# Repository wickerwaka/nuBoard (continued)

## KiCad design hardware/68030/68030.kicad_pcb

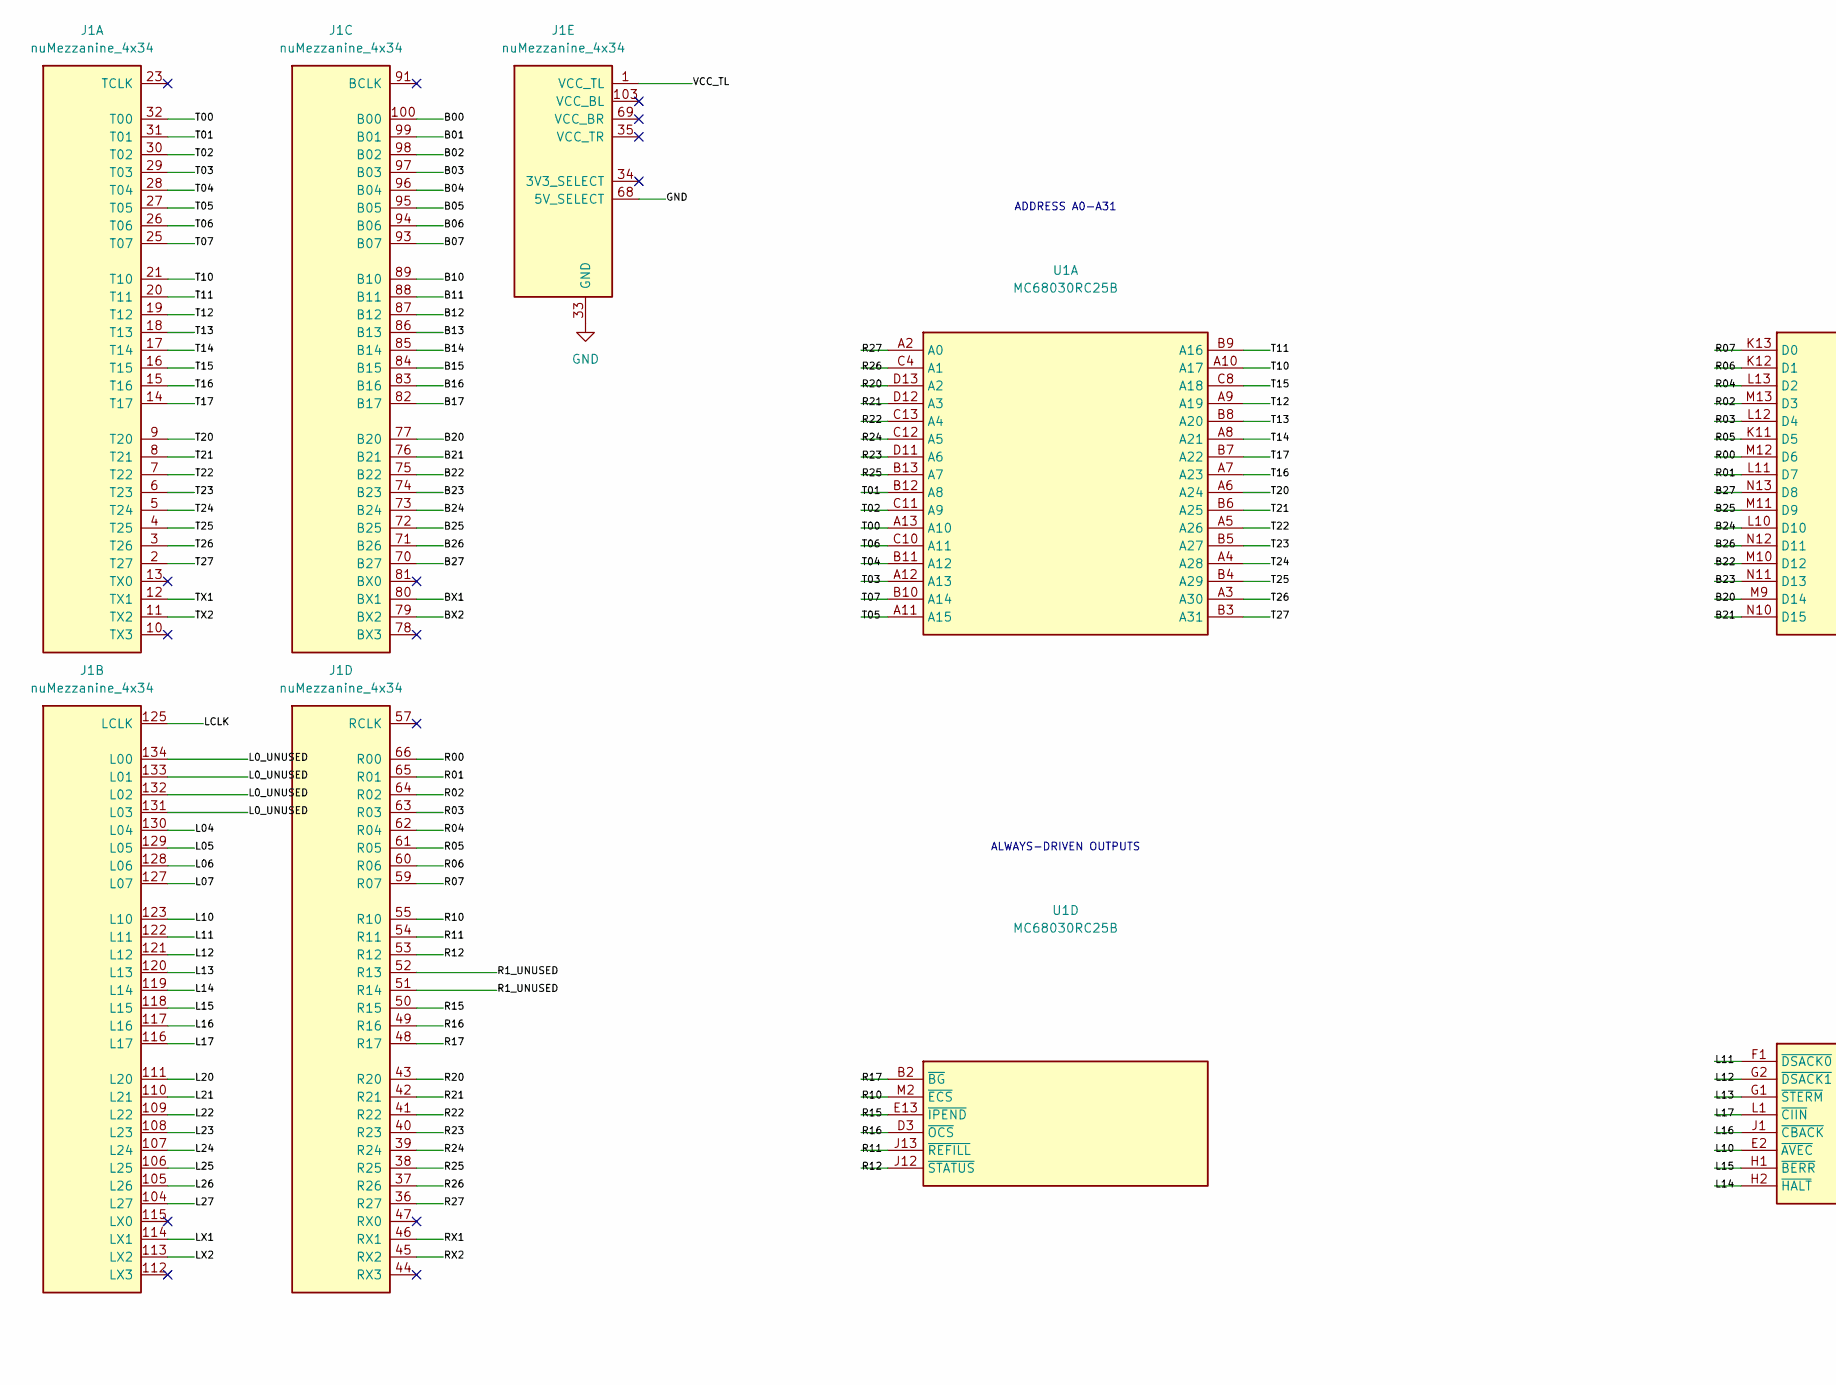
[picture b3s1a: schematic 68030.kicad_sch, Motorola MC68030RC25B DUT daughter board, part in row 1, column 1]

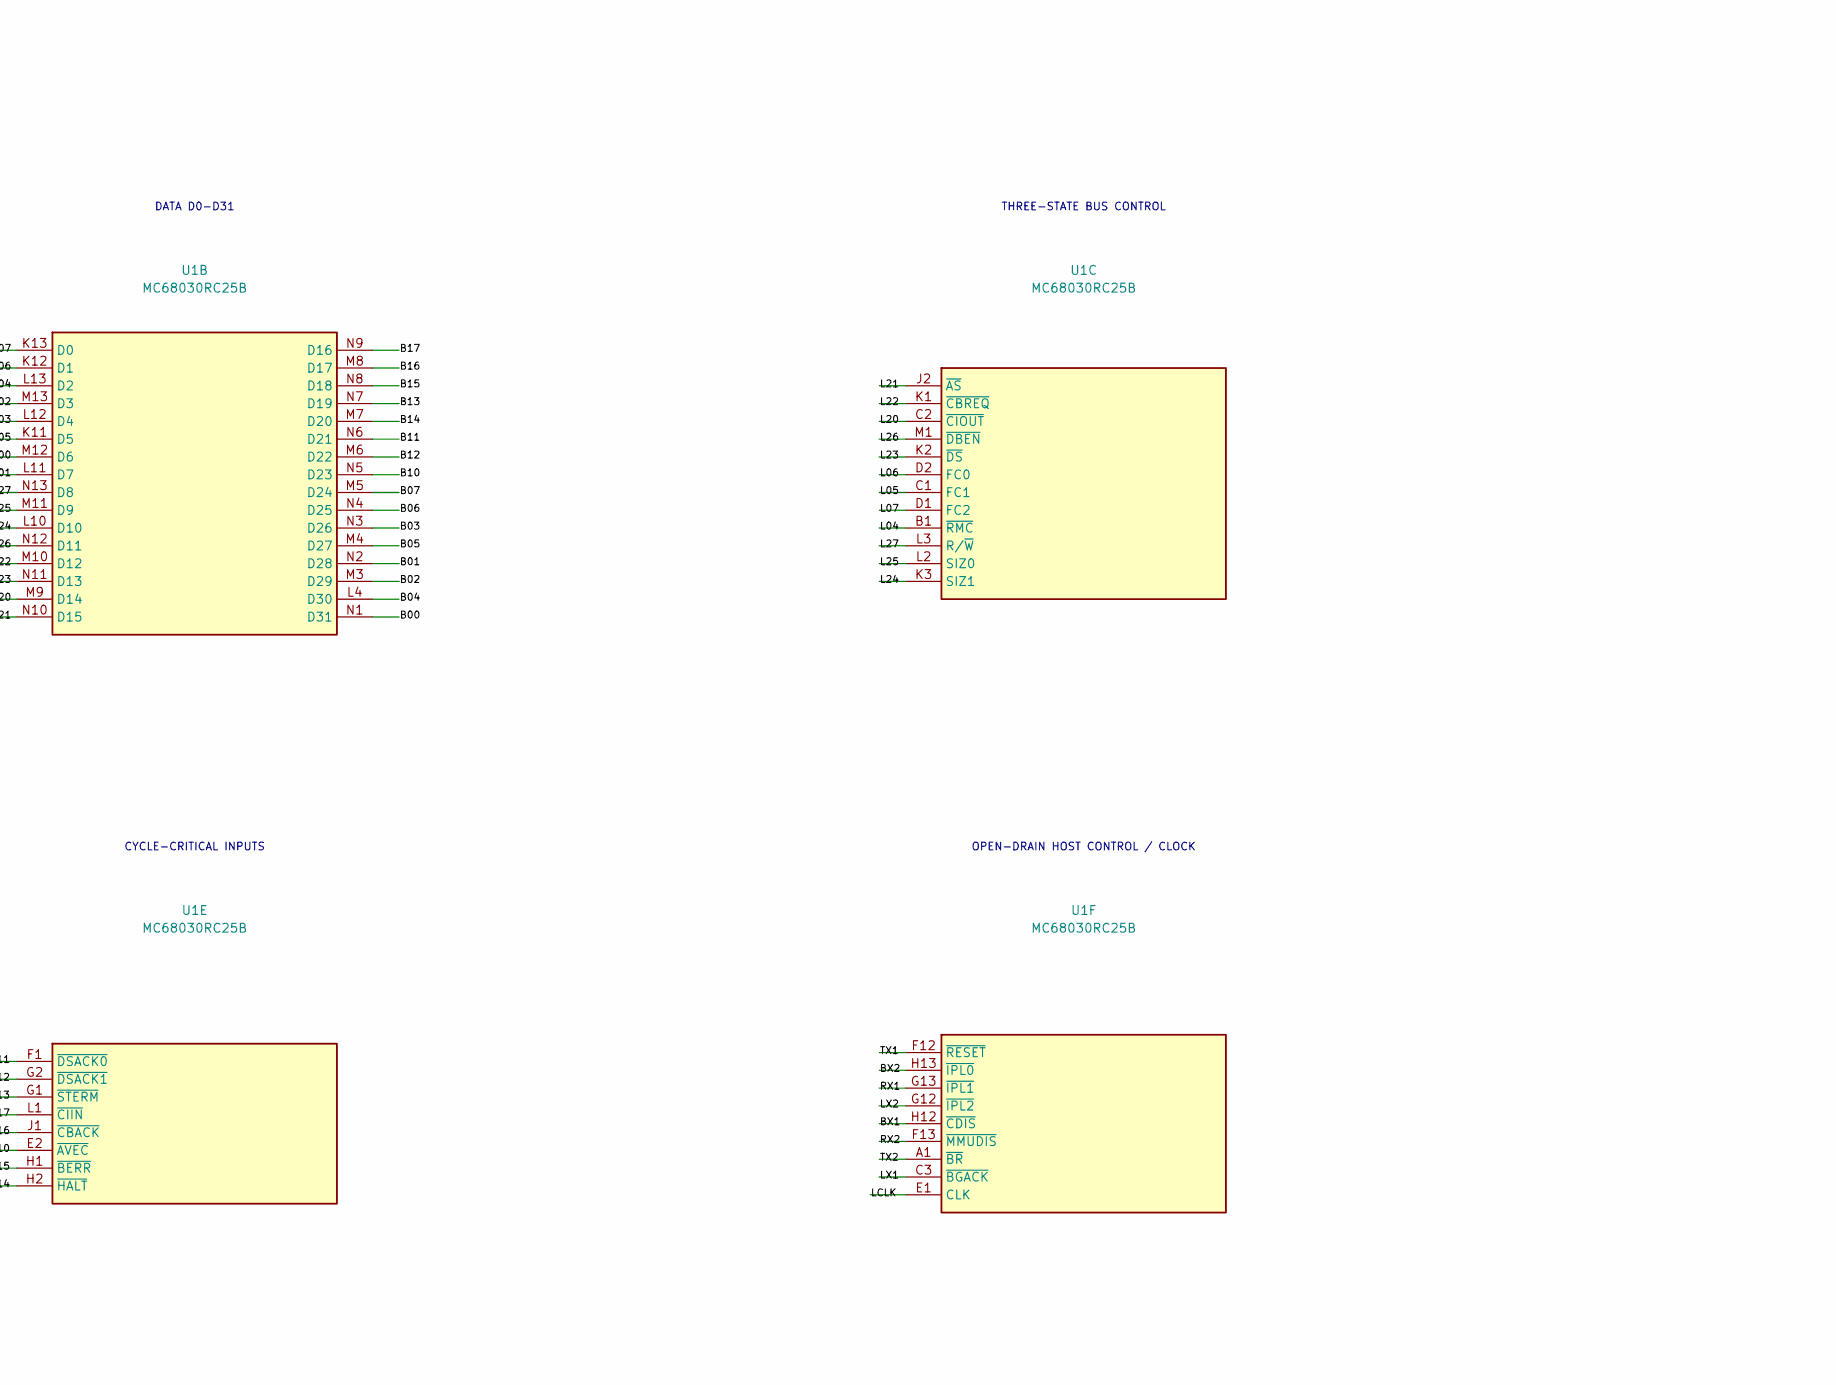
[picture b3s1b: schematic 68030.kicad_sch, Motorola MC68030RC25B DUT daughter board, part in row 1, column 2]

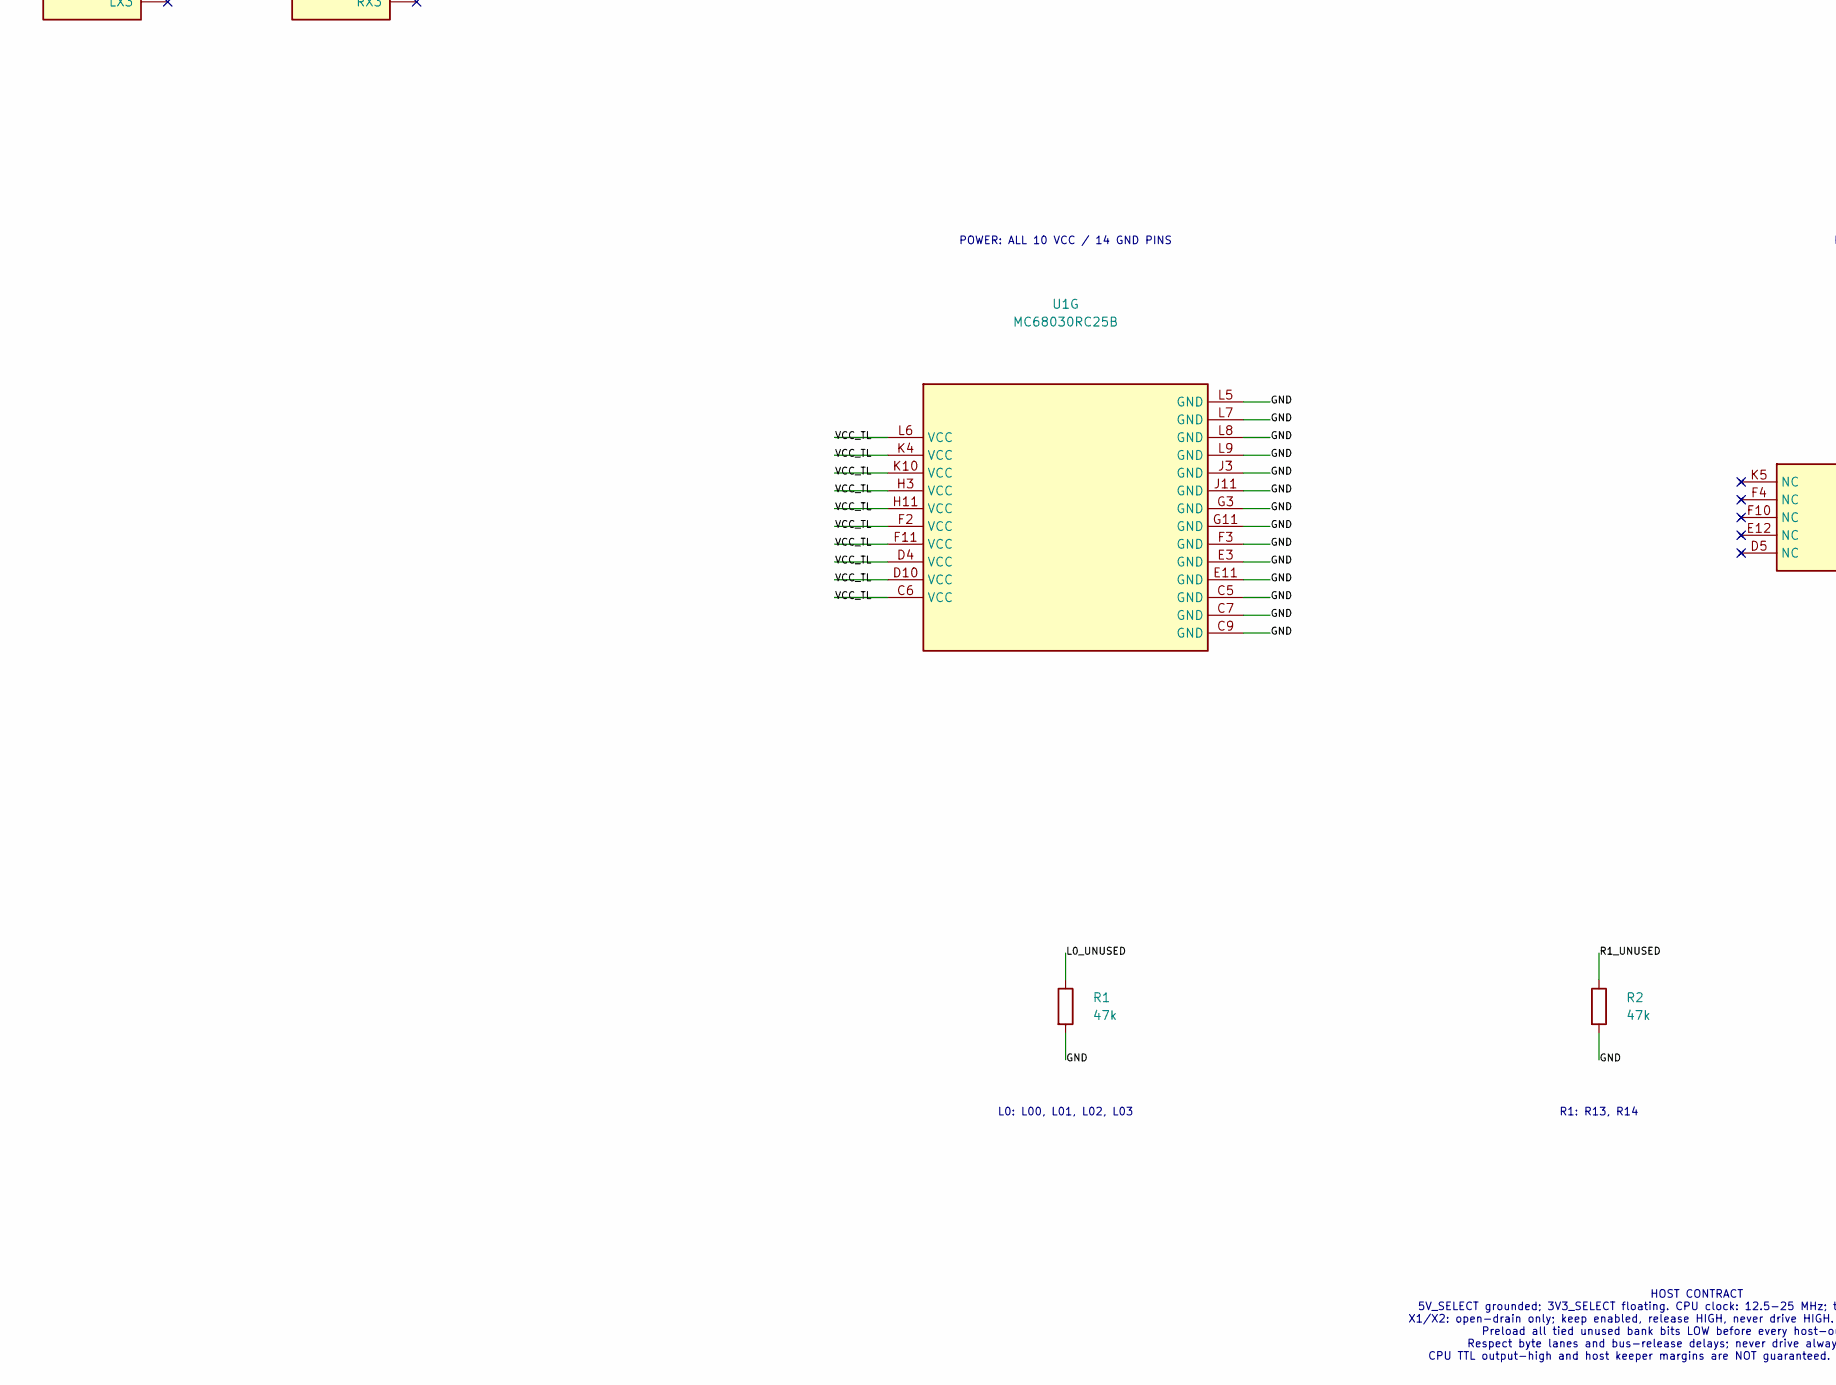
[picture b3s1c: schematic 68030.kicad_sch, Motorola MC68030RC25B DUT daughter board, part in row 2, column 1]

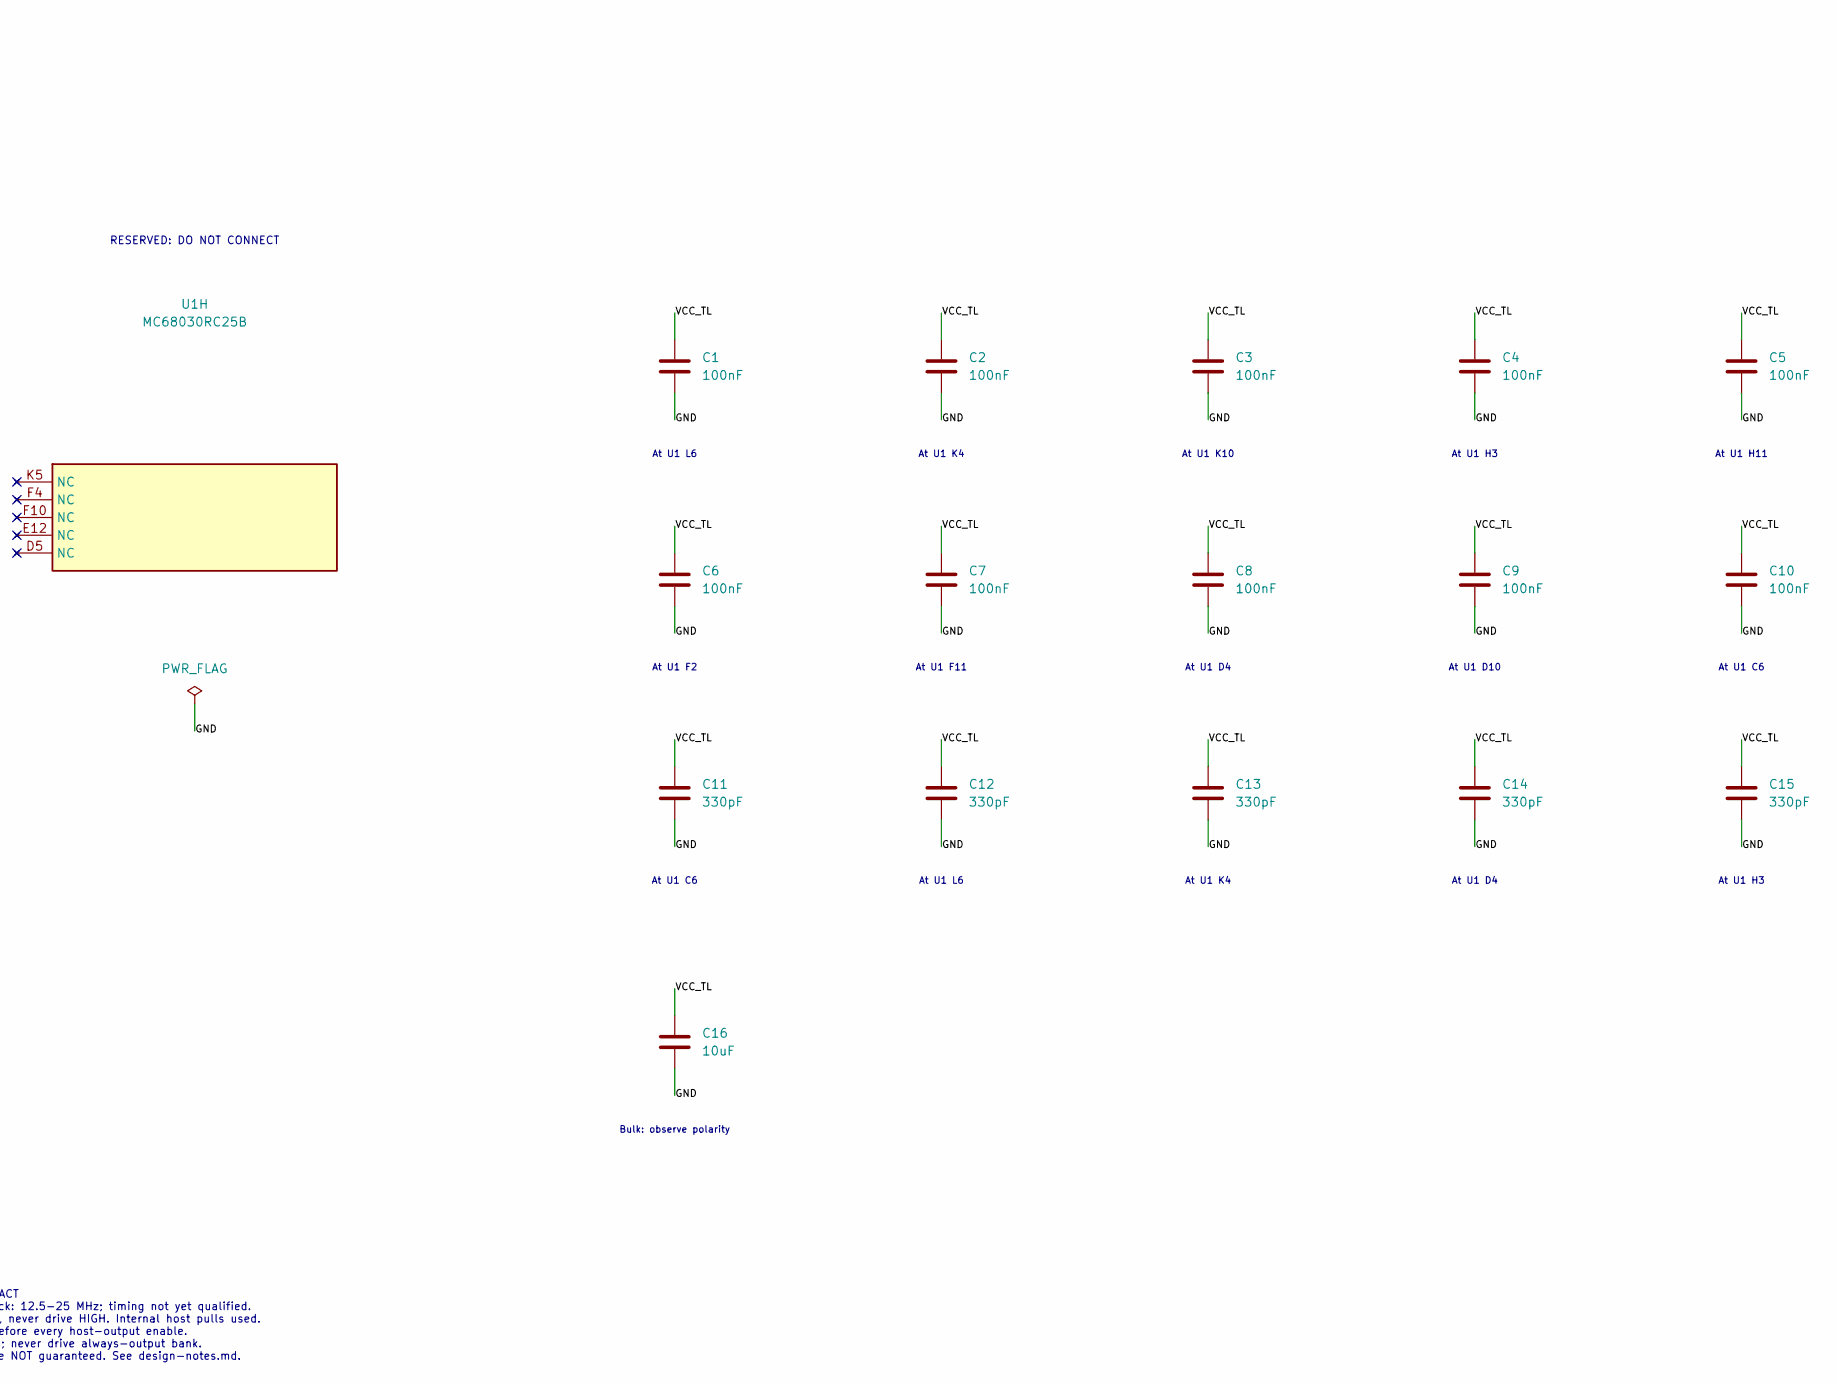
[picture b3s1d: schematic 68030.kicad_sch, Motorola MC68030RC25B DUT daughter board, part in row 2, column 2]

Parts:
C1, C2, C3, C4, C5, C6, C7, C8, C9, C10: 100nF; C_0805_2012Metric_Pad1.18x1.45mm_HandSolder; Voltage 50V
C11, C12, C13, C14, C15: 330pF; C_0805_2012Metric_Pad1.18x1.45mm_HandSolder; Voltage 50V
C16: 10uF; C_0805_2012Metric_Pad1.18x1.45mm_HandSolder; Voltage 25V
J1: nuMezzanine_4x34; nuMezzanine_4x34_P2.54mm
R1, R2: 47k; R_0805_2012Metric_Pad1.20x1.40mm_HandSolder
U1: MC68030RC25B; CPGA-128_MC68030_RC

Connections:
/B00: J1.100 (B00_100), U1.N1 (D31)
/B01: J1.99 (B01_99), U1.N2 (D28)
/B02: J1.98 (B02_98), U1.M3 (D29)
/B03: J1.97 (B03_97), U1.N3 (D26)
/B04: J1.96 (B04_96), U1.L4 (D30)
/B05: J1.95 (B05_95), U1.M4 (D27)
/B06: J1.94 (B06_94), U1.N4 (D25)
/B07: J1.93 (B07_93), U1.M5 (D24)
/B10: J1.89 (B10_89), U1.N5 (D23)
/B11: J1.88 (B11_88), U1.N6 (D21)
/B12: J1.87 (B12_87), U1.M6 (D22)
/B13: J1.86 (B13_86), U1.N7 (D19)
/B14: J1.85 (B14_85), U1.M7 (D20)
/B15: J1.84 (B15_84), U1.N8 (D18)
/B16: J1.83 (B16_83), U1.M8 (D17)
/B17: J1.82 (B17_82), U1.N9 (D16)
/B20: J1.77 (B20_77), U1.M9 (D14)
/B21: J1.76 (B21_76), U1.N10 (D15)
/B22: J1.75 (B22_75), U1.M10 (D12)
/B23: J1.74 (B23_74), U1.N11 (D13)
/B24: J1.73 (B24_73), U1.L10 (D10)
/B25: J1.72 (B25_72), U1.M11 (D9)
/B26: J1.71 (B26_71), U1.N12 (D11)
/B27: J1.70 (B27_70), U1.N13 (D8)
/BX1: J1.80 (BX1_80), U1.H12 (~CDIS)
/BX2: J1.79 (BX2_79), U1.H13 (~IPL0)
/L0_UNUSED: J1.131 (L03_131), J1.132 (L02_132), J1.133 (L01_133), J1.134 (L00_134), R1.1
/L04: J1.130 (L04_130), U1.B1 (~RMC)
/L05: J1.129 (L05_129), U1.C1 (FC1)
/L06: J1.128 (L06_128), U1.D2 (FC0)
/L07: J1.127 (L07_127), U1.D1 (FC2)
/L10: J1.123 (L10_123), U1.E2 (~AVEC)
/L11: J1.122 (L11_122), U1.F1 (~DSACK0)
/L12: J1.121 (L12_121), U1.G2 (~DSACK1)
/L13: J1.120 (L13_120), U1.G1 (~STERM)
/L14: J1.119 (L14_119), U1.H2 (~HALT)
/L15: J1.118 (L15_118), U1.H1 (~BERR)
/L16: J1.117 (L16_117), U1.J1 (~CBACK)
/L17: J1.116 (L17_116), U1.L1 (~CIIN)
/L20: J1.111 (L20_111), U1.C2 (~CIOUT)
/L21: J1.110 (L21_110), U1.J2 (~AS)
/L22: J1.109 (L22_109), U1.K1 (~CBREQ)
/L23: J1.108 (L23_108), U1.K2 (~DS)
/L24: J1.107 (L24_107), U1.K3 (SIZ1)
/L25: J1.106 (L25_106), U1.L2 (SIZ0)
/L26: J1.105 (L26_105), U1.M1 (~DBEN)
/L27: J1.104 (L27_104), U1.L3 (R/~W)
/LCLK: J1.125 (LCLK_125), U1.E1 (CLK)
/LX1: J1.114 (LX1_114), U1.C3 (~BGACK)
/LX2: J1.113 (LX2_113), U1.G12 (~IPL2)
/R00: J1.66 (R00_66), U1.M12 (D6)
/R01: J1.65 (R01_65), U1.L11 (D7)
/R1_UNUSED: J1.51 (R14_51), J1.52 (R13_52), R2.1
/R02: J1.64 (R02_64), U1.M13 (D3)
/R03: J1.63 (R03_63), U1.L12 (D4)
/R04: J1.62 (R04_62), U1.L13 (D2)
/R05: J1.61 (R05_61), U1.K11 (D5)
/R06: J1.60 (R06_60), U1.K12 (D1)
/R07: J1.59 (R07_59), U1.K13 (D0)
/R10: J1.55 (R10_55), U1.M2 (~ECS)
/R11: J1.54 (R11_54), U1.J13 (~REFILL)
/R12: J1.53 (R12_53), U1.J12 (~STATUS)
/R15: J1.50 (R15_50), U1.E13 (~IPEND)
/R16: J1.49 (R16_49), U1.D3 (~OCS)
/R17: J1.48 (R17_48), U1.B2 (~BG)
/R20: J1.43 (R20_43), U1.D13 (A2)
/R21: J1.42 (R21_42), U1.D12 (A3)
/R22: J1.41 (R22_41), U1.C13 (A4)
/R23: J1.40 (R23_40), U1.D11 (A6)
/R24: J1.39 (R24_39), U1.C12 (A5)
/R25: J1.38 (R25_38), U1.B13 (A7)
/R26: J1.37 (R26_37), U1.C4 (A1)
/R27: J1.36 (R27_36), U1.A2 (A0)
/RX1: J1.46 (RX1_46), U1.G13 (~IPL1)
/RX2: J1.45 (RX2_45), U1.F13 (~MMUDIS)
/T00: J1.32 (T00_32), U1.A13 (A10)
/T01: J1.31 (T01_31), U1.B12 (A8)
/T02: J1.30 (T02_30), U1.C11 (A9)
/T03: J1.29 (T03_29), U1.A12 (A13)
/T04: J1.28 (T04_28), U1.B11 (A12)
/T05: J1.27 (T05_27), U1.A11 (A15)
/T06: J1.26 (T06_26), U1.C10 (A11)
/T07: J1.25 (T07_25), U1.B10 (A14)
/T10: J1.21 (T10_21), U1.A10 (A17)
/T11: J1.20 (T11_20), U1.B9 (A16)
/T12: J1.19 (T12_19), U1.A9 (A19)
/T13: J1.18 (T13_18), U1.B8 (A20)
/T14: J1.17 (T14_17), U1.A8 (A21)
/T15: J1.16 (T15_16), U1.C8 (A18)
/T16: J1.15 (T16_15), U1.A7 (A23)
/T17: J1.14 (T17_14), U1.B7 (A22)
/T20: J1.9 (T20_9), U1.A6 (A24)
/T21: J1.8 (T21_8), U1.B6 (A25)
/T22: J1.7 (T22_7), U1.A5 (A26)
/T23: J1.6 (T23_6), U1.B5 (A27)
/T24: J1.5 (T24_5), U1.A4 (A28)
/T25: J1.4 (T25_4), U1.B4 (A29)
/T26: J1.3 (T26_3), U1.A3 (A30)
/T27: J1.2 (T27_2), U1.B3 (A31)
/TX1: J1.12 (TX1_12), U1.F12 (~RESET)
/TX2: J1.11 (TX2_11), U1.A1 (~BR)
/VCC_TL: C1.1, C2.1, C3.1, C4.1, C5.1, C6.1, C7.1, C8.1, C9.1, C10.1, C11.1, C12.1, C13.1, C14.1, C15.1, C16.1, J1.1 (VCC_TL_1), U1.C6 (VCC), U1.D4 (VCC), U1.D10 (VCC), U1.F2 (VCC), U1.F11 (VCC), U1.H3 (VCC), U1.H11 (VCC), U1.K4 (VCC), U1.K10 (VCC), U1.L6 (VCC)
GND: C1.2, C2.2, C3.2, C4.2, C5.2, C6.2, C7.2, C8.2, C9.2, C10.2, C11.2, C12.2, C13.2, C14.2, C15.2, C16.2, J1.22 (GND_22), J1.24 (GND_24), J1.33 (GND_33), J1.56 (GND_56), J1.58 (GND_58), J1.67 (GND_67), J1.68 (5V_SELECT_68), J1.90 (GND_90), J1.92 (GND_92), J1.101 (GND_101), J1.102 (GND), J1.124 (GND_124), J1.126 (GND_126), J1.135 (GND_135), J1.136 (GND), R1.2, R2.2, U1.C5 (GND), U1.C7 (GND), U1.C9 (GND), U1.E3 (GND), U1.E11 (GND), U1.F3 (GND), U1.G3 (GND), U1.G11 (GND), U1.J3 (GND), U1.J11 (GND), U1.L5 (GND), U1.L7 (GND), U1.L8 (GND), U1.L9 (GND)

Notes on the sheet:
ADDRESS A0-A31
DATA D0-D31
THREE-STATE BUS CONTROL
ALWAYS-DRIVEN OUTPUTS
CYCLE-CRITICAL INPUTS
OPEN-DRAIN HOST CONTROL / CLOCK
POWER: ALL 10 VCC / 14 GND PINS
RESERVED: DO NOT CONNECT
At U1 L6
At U1 K4
At U1 K10
At U1 H3
At U1 H11
At U1 F2
At U1 F11
At U1 D4
At U1 D10
At U1 C6
Bulk: observe polarity
L0: L00, L01, L02, L03
R1: R13, R14
HOST CONTRACT 5V_SELECT grounded; 3V3_SELECT floating. CPU clock: 12.5-25 MHz; timing not yet qualified. X1/X2: open-drain only; keep enabled, release HIGH, never drive HIGH. Internal host pulls used. Preload all tied unused bank bits LOW before every host-output enable. Respect byte lanes and bus-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

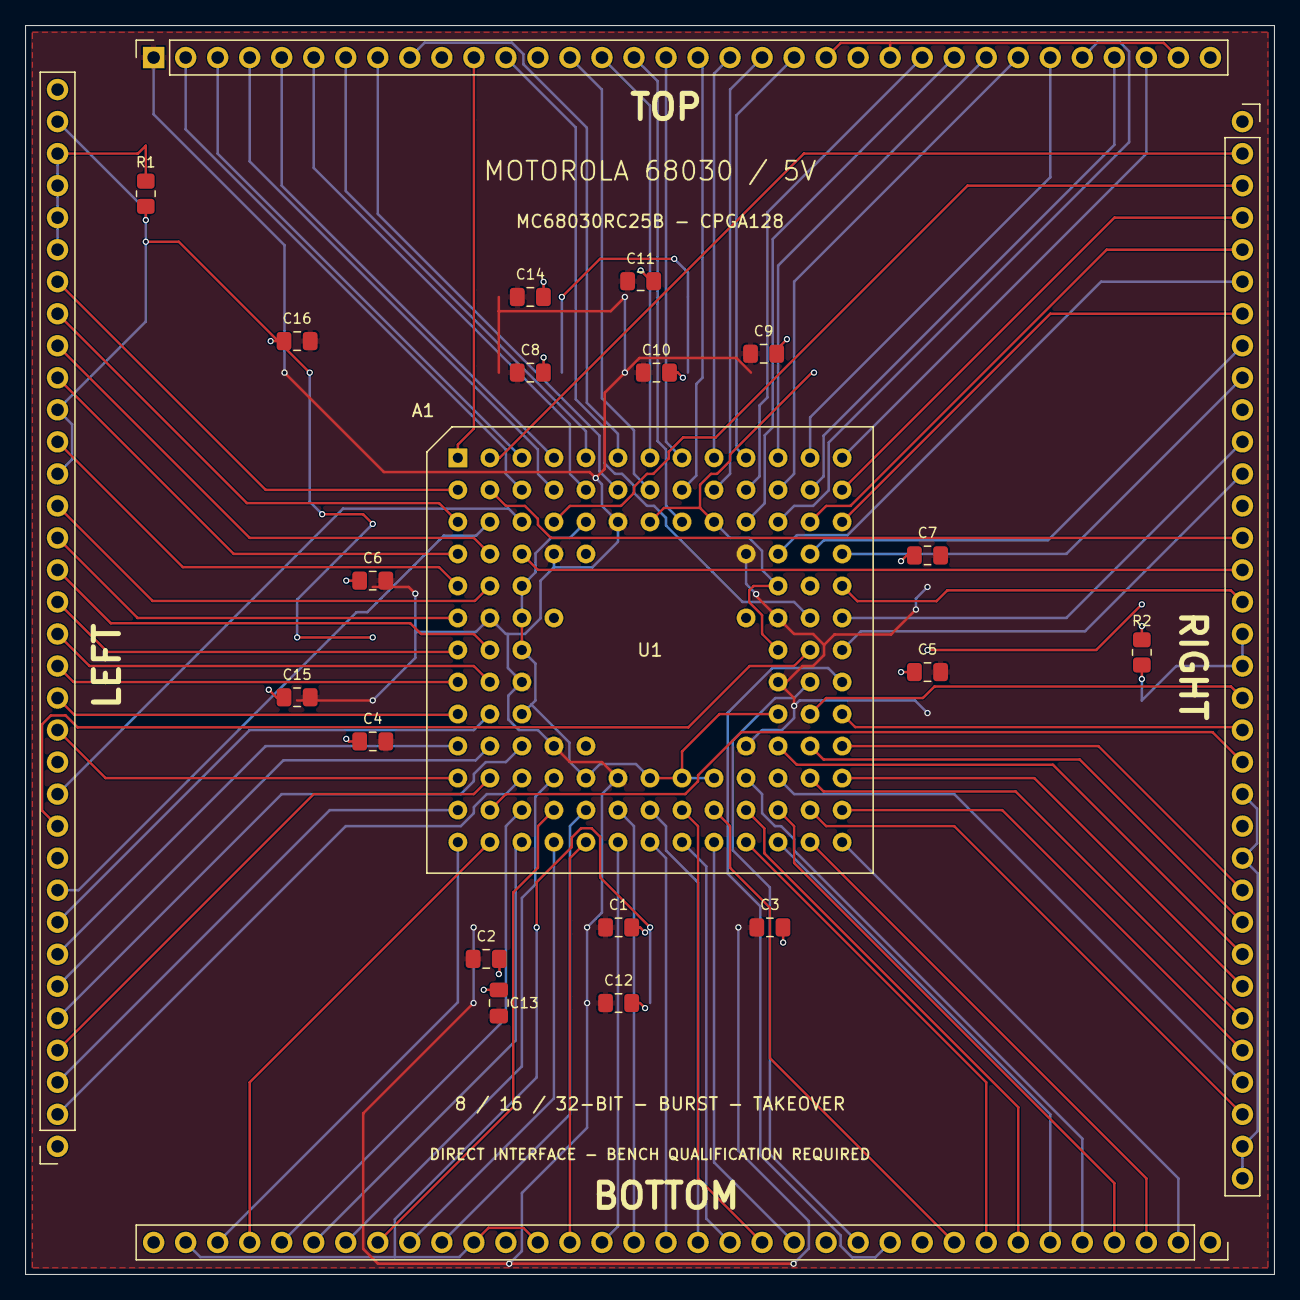
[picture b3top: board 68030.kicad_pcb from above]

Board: 2 copper layers, 99.1 x 99.1 mm, 20 parts (0 on the bottom side), 103 nets.

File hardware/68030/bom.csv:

References,Quantity,Value / part,Package,Notes
U1,1,Motorola MC68030RC25B,CPGA128 CASE789C-01,Direct CPU pin mounting; no socket qualified
C1 C2 C3 C4 C5 C6 C7 C8 C9 C10,10,100nF X7R ceramic >=50V,0805 SMD HandSolder,one per VCC pin
C11 C12 C13 C14 C15,5,330pF C0G ceramic >=50V,0805 SMD HandSolder,Supplementary high-frequency bypass; 0805 C0G
C16,1,10uF X7R/X5R MLCC >=25V,0805 SMD HandSolder,Nonpolar; check effective capacitance at 5V DC bias
R1 R2,2,47k 1% >=0.25W,0805 SMD HandSolder,One shared unused-bit pull-down per partially used bank
J1,1,nuBoard mating contact set,"Four 34-position rows, 2.54mm pitch",Match host mating geometry and height

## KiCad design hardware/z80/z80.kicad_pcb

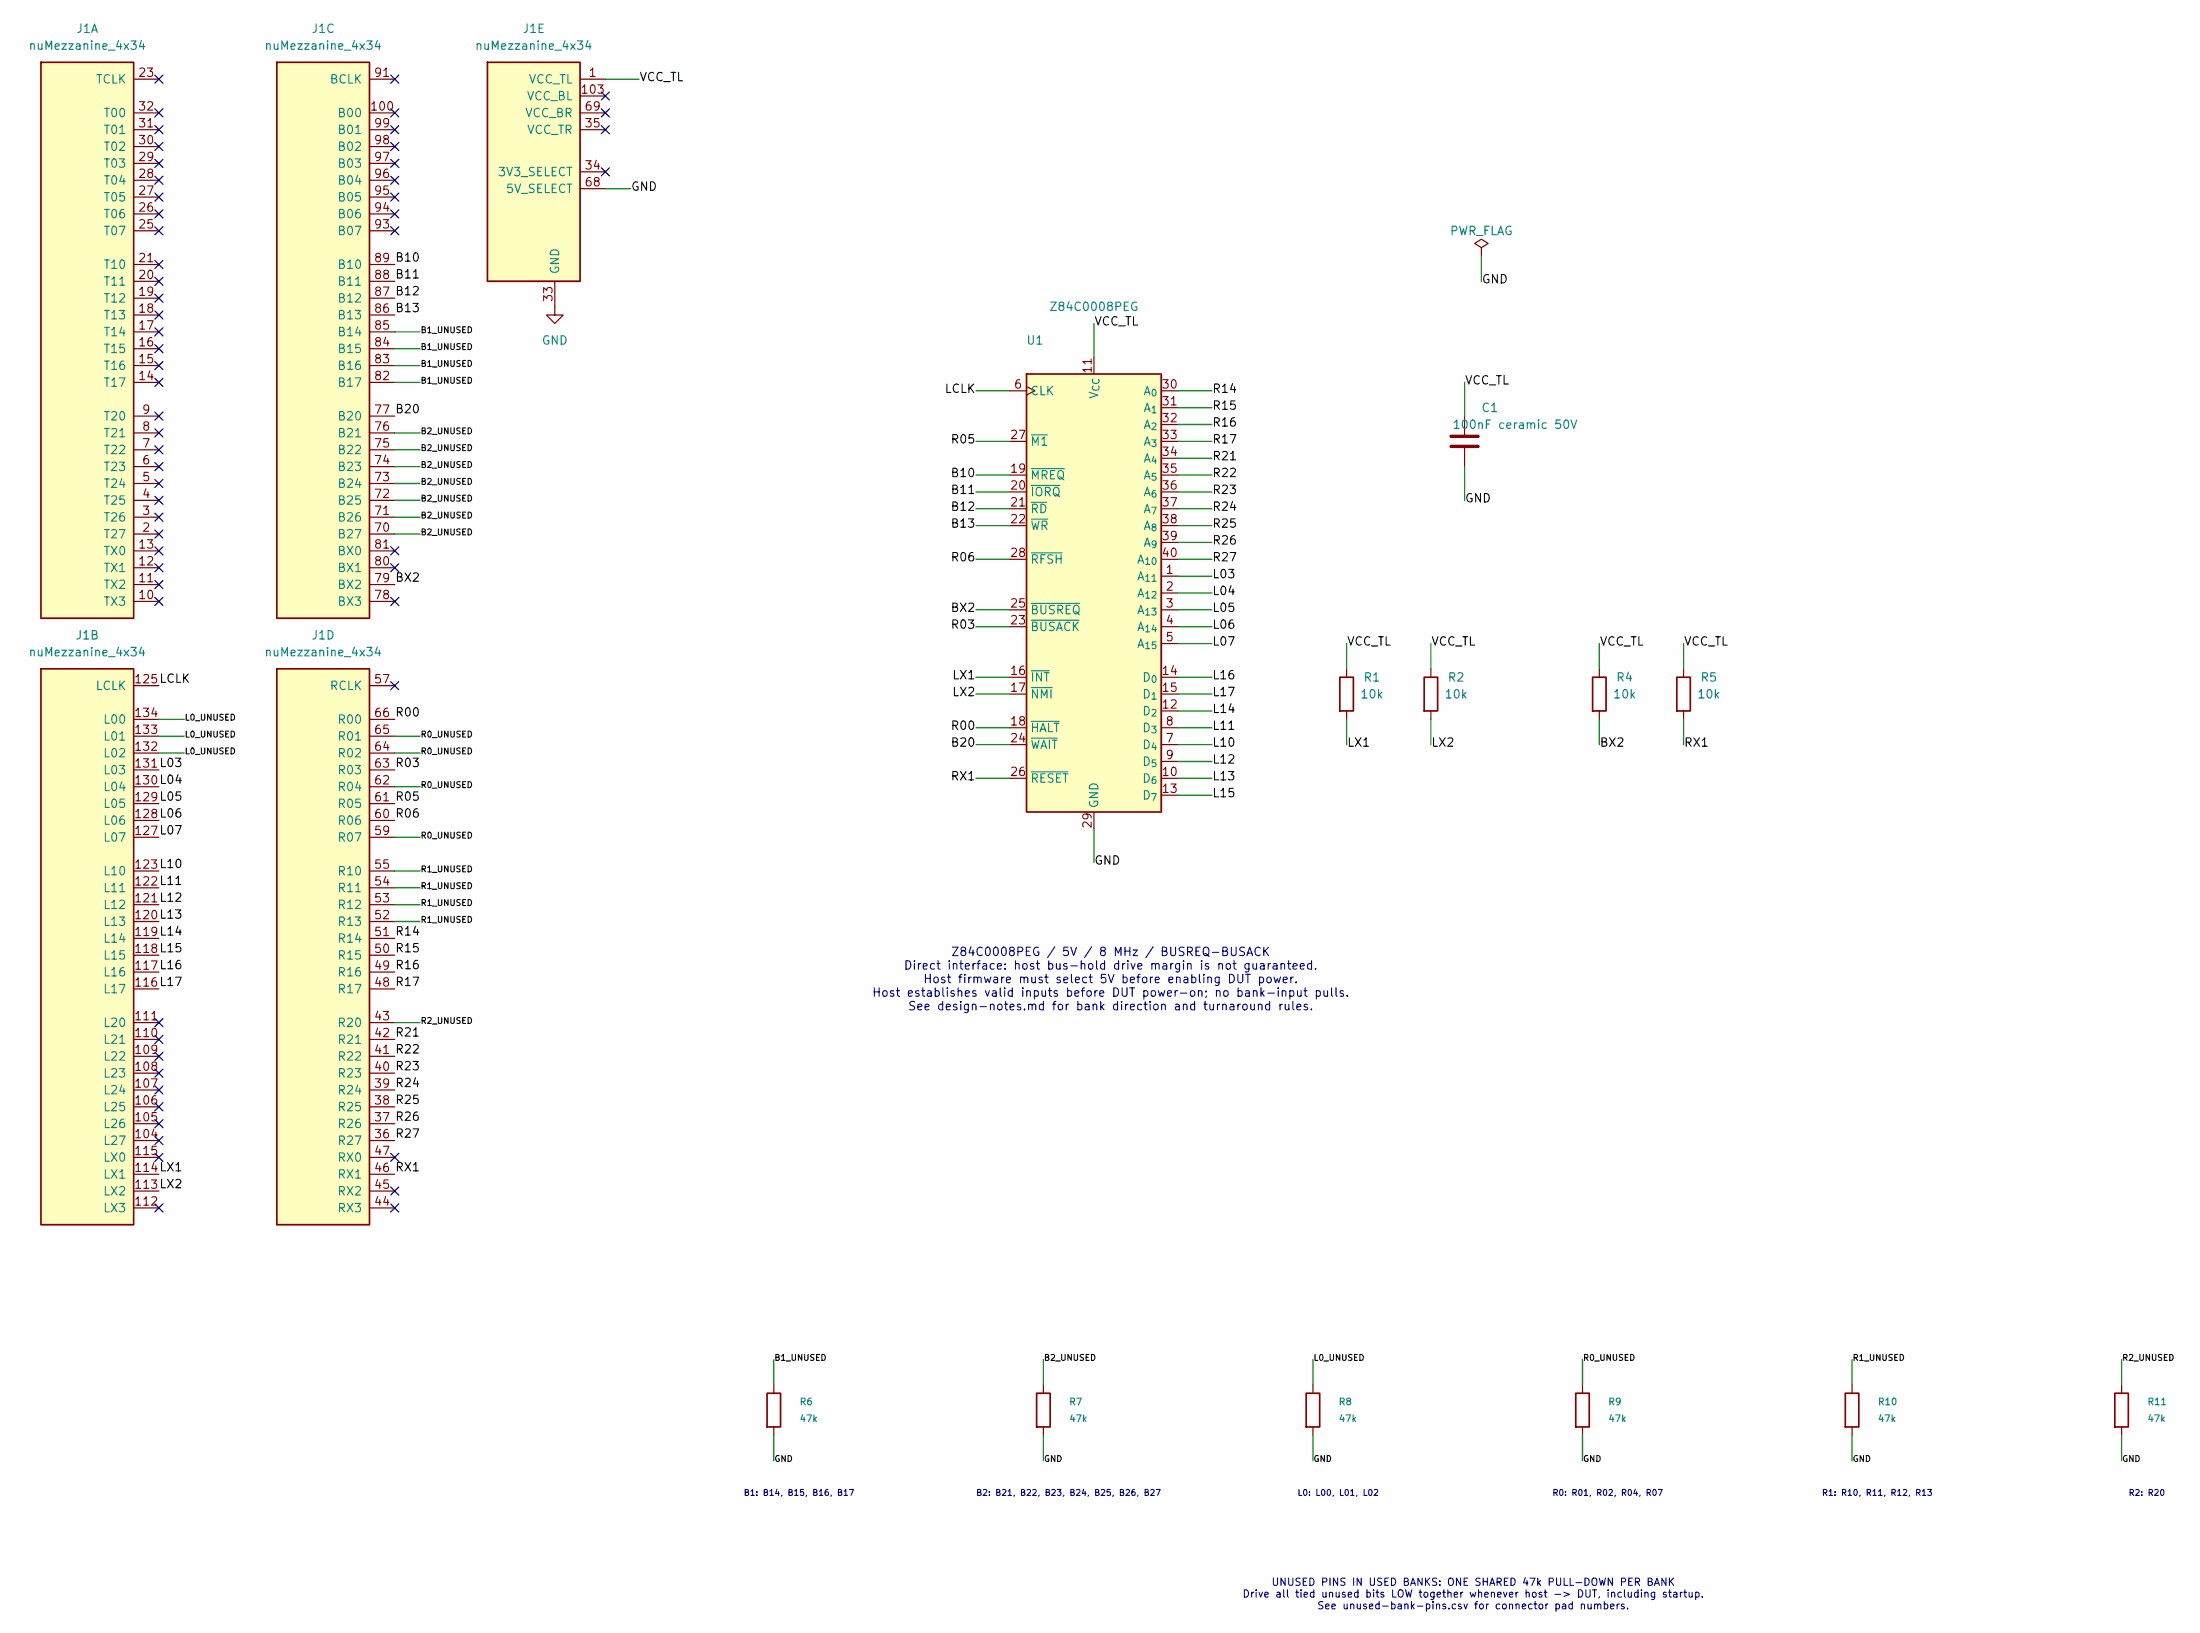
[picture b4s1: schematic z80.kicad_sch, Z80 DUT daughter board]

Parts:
C1: 100nF ceramic 50V; C_0805_2012Metric_Pad1.18x1.45mm_HandSolder
J1: nuMezzanine_4x34; nuMezzanine_4x34_P2.54mm
R1, R2, R4, R5: 10k; R_0805_2012Metric_Pad1.20x1.40mm_HandSolder
R6, R7, R8, R9, R10, R11: 47k; R_0805_2012Metric_Pad1.20x1.40mm_HandSolder
U1: Z84C0008PEG; DIP-40_W15.24mm_Socket

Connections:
/B1_UNUSED: J1.82 (B17_82), J1.83 (B16_83), J1.84 (B15_84), J1.85 (B14_85), R6.1
/B2_UNUSED: J1.70 (B27_70), J1.71 (B26_71), J1.72 (B25_72), J1.73 (B24_73), J1.74 (B23_74), J1.75 (B22_75), J1.76 (B21_76), R7.1
/B10: J1.89 (B10_89), U1.19 (~MREQ)
/B11: J1.88 (B11_88), U1.20 (~IORQ)
/B12: J1.87 (B12_87), U1.21 (~RD)
/B13: J1.86 (B13_86), U1.22 (~WR)
/B20: J1.77 (B20_77), U1.24 (~WAIT)
/BX2: J1.79 (BX2_79), R4.2, U1.25 (~BUSREQ)
/L0_UNUSED: J1.132 (L02_132), J1.133 (L01_133), J1.134 (L00_134), R8.1
/L03: J1.131 (L03_131), U1.1 (A_{11})
/L04: J1.130 (L04_130), U1.2 (A_{12})
/L05: J1.129 (L05_129), U1.3 (A_{13})
/L06: J1.128 (L06_128), U1.4 (A_{14})
/L07: J1.127 (L07_127), U1.5 (A_{15})
/L10: J1.123 (L10_123), U1.7 (D_{4})
/L11: J1.122 (L11_122), U1.8 (D_{3})
/L12: J1.121 (L12_121), U1.9 (D_{5})
/L13: J1.120 (L13_120), U1.10 (D_{6})
/L14: J1.119 (L14_119), U1.12 (D_{2})
/L15: J1.118 (L15_118), U1.13 (D_{7})
/L16: J1.117 (L16_117), U1.14 (D_{0})
/L17: J1.116 (L17_116), U1.15 (D_{1})
/LCLK: J1.125 (LCLK_125), U1.6 (CLK)
/LX1: J1.114 (LX1_114), R1.2, U1.16 (~INT)
/LX2: J1.113 (LX2_113), R2.2, U1.17 (~NMI)
/R00: J1.66 (R00_66), U1.18 (~HALT)
/R0_UNUSED: J1.59 (R07_59), J1.62 (R04_62), J1.64 (R02_64), J1.65 (R01_65), R9.1
/R1_UNUSED: J1.52 (R13_52), J1.53 (R12_53), J1.54 (R11_54), J1.55 (R10_55), R10.1
/R2_UNUSED: J1.43 (R20_43), R11.1
/R03: J1.63 (R03_63), U1.23 (~BUSACK)
/R05: J1.61 (R05_61), U1.27 (~M1)
/R06: J1.60 (R06_60), U1.28 (~RFSH)
/R14: J1.51 (R14_51), U1.30 (A_{0})
/R15: J1.50 (R15_50), U1.31 (A_{1})
/R16: J1.49 (R16_49), U1.32 (A_{2})
/R17: J1.48 (R17_48), U1.33 (A_{3})
/R21: J1.42 (R21_42), U1.34 (A_{4})
/R22: J1.41 (R22_41), U1.35 (A_{5})
/R23: J1.40 (R23_40), U1.36 (A_{6})
/R24: J1.39 (R24_39), U1.37 (A_{7})
/R25: J1.38 (R25_38), U1.38 (A_{8})
/R26: J1.37 (R26_37), U1.39 (A_{9})
/R27: J1.36 (R27_36), U1.40 (A_{10})
/RX1: J1.46 (RX1_46), R5.2, U1.26 (~RESET)
/VCC_TL: C1.1, J1.1 (VCC_TL_1), R1.1, R2.1, R4.1, R5.1, U1.11 (V_{CC})
GND: C1.2, J1.22 (GND_22), J1.24 (GND_24), J1.33 (GND_33), J1.56 (GND_56), J1.58 (GND_58), J1.67 (GND_67), J1.68 (5V_SELECT_68), J1.90 (GND_90), J1.92 (GND_92), J1.101 (GND_101), J1.102 (GND), J1.124 (GND_124), J1.126 (GND_126), J1.135 (GND_135), J1.136 (GND), R6.2, R7.2, R8.2, R9.2, R10.2, R11.2, U1.29 (GND)

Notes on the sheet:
Z84C0008PEG / 5V / 8 MHz / BUSREQ-BUSACK Direct interface: host bus-hold drive margin is not guaranteed. Host firmware must select 5V before enabling DUT power. Host establishes valid inputs before DUT power-on; no bank-input pulls. See design-notes.md for bank direction and turnaround rules.
B1: B14, B15, B16, B17
B2: B21, B22, B23, B24, B25, B26, B27
L0: L00, L01, L02
R0: R01, R02, R04, R07
R1: R10, R11, R12, R13
R2: R20
UNUSED PINS IN USED BANKS: ONE SHARED 47k PULL-DOWN PER BANK Drive all tied unused bits LOW together whenever host -> DUT, including startup. See unused-bank-pins.csv for connector pad numbers.
